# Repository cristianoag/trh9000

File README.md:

# TRH9000
The Yamaha V9990 based open-source video card for the MSX

## Introduction

If you ever spent just a few minutes on YouTube searching for MSX content, I bet you certainly found some footage covering the V9990. Well, not specifically the V9990 chip, but video cards based on it.

The first video card based on the unreleased, kind of obscure Yamaha V9990 VDP chip was the Graphics9000 (or GFX9000). The GFX9000 is (was) a graphics expansion device for MSX computers developed by Sunrise in 1994.

It was designed as an expansion cartridge for the MSX standard that can be installed in a slot on a computer that also connects to the computer’s video output and monitor. The device works as an additional independent video controller.

The device is based on the Yamaha V9990 video controller (VDP). The chip was designed specifically for use in computers of the alleged but not implemented (by the time of this writing) MSX3 standard. The V9990 is not backward compatible with the V99x8 chips, and thus cannot be used as the main video controller of standard MSX-compatible computers.

## The TRH9000

TRH9000 is an open-source implementation of the GFX9000, representing a community-driven effort to document everything necessary to build MSX cartridges that can run V9990 software.

| PCB Front | PCB Back |
| --- | --- |
|  |  |

The goal is to make those cards more accessible and improve the amount of software available for it. 

## Technical Information

The TRH9000 is a graphics expansion cartridge designed for MSX computers that was developed by a community of MSX enthusiasts as an open-source implementation of the GFX9000. 

### Selection Logic
For the TRH9000, the control logic is implemented by two ICs. According to the not exhaustive list of IO ports documented [here](https://www.msx.org/wiki/I/O_Ports_List). The IO ports used the by an GFX9000 compatible cartridge must be 60h~6Fh*. The 74LS138 IC on the board performs the selection of those IO ports and with the aid of the 74LS32 performs the activation of the appropriate signals on the V9990 chip.

> **Note:** Very important to use the 74LS138 and 74LS32 ICs. The 74HC138 and 74HC32 are not 100% compatible with the logic levels used by old MSX computers and if used, the cartridge may not work properly. 74HCT138 and 74HCT32 are also compatible with the old logic levels and can be used as a replacement.

### RAM chips

The KM428C256 RAM chip is the primary memory module used in the TRH9000. It is a CMOS 256K x 8 bit dual-port dynamic random-access memory (DRAM) chip that serves as the primary memory module in the cartridge. We use two memory chips, wired to the Yamaha V9990 VDP.

### Connectors

On its latest version, the TRH9000 features three types of video output connectors: a DB15 RGB/VGA connector, a RCA composite connector and a mini-DIN 4 SVideo connector. The DB15 connector is a standard video connector that supports VGA, and RGB, making it a versatile choice for connecting to various types of displays. The SVIDEO signal, on the other hand, is a video signal that carries the chrominance and luminance components of the video separately, resulting in a higher quality image than composite video that is output on the RCA connector. 

### Video Output

#### RGB 
The TRH9000 cartridge produces RGB signal with a horizontal frequency of 15.7KHz, which was the standard at the time of the V9990 chip's release. If you plan to connect the cartridge directly to your monitor using a VGA cable, it's important to ensure that your monitor supports synchronization at 15.7KHz.

You can see a list of modern monitors with support to 15.7KHz available at http://15khz.wikidot.com/

If you're not getting any image from the cartridge connector, it indicates that your monitor cannot sync at 15.7KHz. Typically, modern monitors can only sync at frequencies above 31KHz.

In such a scenario, you will require an adapter to upscale the frequency, making it compatible with your monitor. These adapters are commonly used for vintage video games and are readily available in various marketplaces. Here are a few options to consider:

||Description|Link|
|--|--|--|
||TZT HamGeek GBSC Converter GBS Control Retro Video Game Signal Converter Gaming Accessory  |[Ali Express](https://s.click.aliexpress.com/e/_DcZRM6T)
||OSSC HDMI-Compatible Converter Open Source Scan Adapter Kit with Game Cable for Retro Game Consoles  |[Ali Express](https://s.click.aliexpress.com/e/_DnNQGvv)
||Retrotink 2X Scart | https://www.retrotink.com/product-page/retrotink-2x-scart

If you decide to use the Retrotink you will need a VGA to SCART cable. That is easy to solder and you need to connect the signals in the following way:

|VGA||SCART|Signal|
|-|-|-|-|
|1|-->|15 |Red
|2|-->|11| Green
|3|--> |7 |Blue
|5|--> |21 |GND
|13|-->|20| Sync

By request of the community, a jumper was included on the latest PCB version to provide optionally 5V on the pin 9 of the VGA connector. This is useful for those who want to use build a SCART cable that depending on the monitor may require 5V in some pins. 

The jumper is located on the back of the PCB and is labeled as "JP1". The default position is open, so if you need to use it, you will need to close it with a solder blob.

Here is a diagram of the DH15 connector:

#### S-Video and Composite

The TRH9000 cartridge provides support for both S-Video and Composite video outputs. These video signals are transmitted through respective connectors that are located on the upper edge of the cartridge PCB. 

## Bill of Materials

[TRH9000 Interactive BOM](https://htmlpreview.github.io/?https://github.com/cristianoag/trh9000/blob/main/Hardware/Kicad/TRH9000_1.7/bom/ibom.html)

|References|Value|Footprint|Qtd|Link|
|-|-|-|-|-|
|C1, C6, C7, C8, C17, C19, C20, C22, C24	|0.1uF	|C_0805_2012Metric	|9|[Ali Express](https://s.click.aliexpress.com/e/_DkAAT2J)
|C9, C11, C12, C13, C14, C15, C26|	220uF	|CP_EIA-3528-15_AVX-H|	7|[Ali Express](https://s.click.aliexpress.com/e/_DCrPttV)
|C3, C4	|27pF|	C_0805_2012Metric|	2|[Ali Express](https://s.click.aliexpress.com/e/_DkAAT2J)
|C5, C10|	47pF	|C_0805_2012Metric|	2|[Ali Express](https://s.click.aliexpress.com/e/_DkAAT2J)
|C16, C18|	1uF	|C_0805_2012Metric	|2|[Ali Express](https://s.click.aliexpress.com/e/_DkAAT2J)
|C23, C25|	10nF|	C_0805_2012Metric|	2|[Ali Express](https://s.click.aliexpress.com/e/_DkAAT2J)
|C2|	10uF|	C_0805_2012Metric	|1|[Ali Express](https://s.click.aliexpress.com/e/_DkAAT2J)
|C21|	47uF|	CP_EIA-3528-15_AVX-H|	1|[Ali Express](https://s.click.aliexpress.com/e/_DCrPttV)
|R1, R3, R4, R5, R6, R10|	4K7	|R_0805_2012Metric|	6|[Ali Express](https://s.click.aliexpress.com/e/_DEyTmBN)
|R14, R15, R16, R17, R18, R19|	75R	|R_0805_2012Metric|	6|[Ali Express](https://s.click.aliexpress.com/e/_DEyTmBN)
|R20,R21,R22|470R|R_0805_2012Metric|3|[Ali Express](https://s.click.aliexpress.com/e/_DEyTmBN)
|R7, R12|	2K2	|R_0805_2012Metric|	2|[Ali Express](https://s.click.aliexpress.com/e/_DEyTmBN)
|			R2	|10M	|R_0805_2012Metric|	1|[Ali Express](https://s.click.aliexpress.com/e/_DEyTmBN)
|			R8	|1K	|R_0805_2012Metric|	1|[Ali Express](https://s.click.aliexpress.com/e/_DEyTmBN)
|			R9	|100R	|R_0805_2012Metric|	1|[Ali Express](https://s.click.aliexpress.com/e/_DEyTmBN)
|			R11	|220R	|R_0805_2012Metric	|1|[Ali Express](https://s.click.aliexpress.com/e/_DEyTmBN)
|			R13	|3K3|	R_0805_2012Metric	|1|[Ali Express](https://s.click.aliexpress.com/e/_DEyTmBN)
|			L1, L2|	4.7uH|	L_0805_2012Metric	|2|[Ali Express](https://s.click.aliexpress.com/e/_Dern3vN)
|			U4, U5	|KM428C256	|SOJ-40_400mil|	2|[UT Source](https://www.utsource.net/itm/p/781989.html)
|			U1	|74HC138	|SO-16_3.9x9.9mm_P1.27mm	|1|[Ali Express](https://s.click.aliexpress.com/e/_De0MrAf)
|			U2	|74HC32	|SO-14_3.9x8.65mm_P1.27mm|	1|[Ali Express](https://s.click.aliexpress.com/e/_DlCjJDN)
|			U3|	V9990|	LQFP-128_28x28mm_P0.8mm	|1|[The Retro Hacker Store](https://theretrohacker.com/product/v9990-non-vga-video-controller-ic-qfp-128/)
|			U6	|CXA2075M	|SOP-24_7.5x15.4mm_P1.27mm|	1|[Ali Express](https://s.click.aliexpress.com/e/_DBjZMTN)
|			Y1	|21.47727Mhz	|Crystal_HC49-U_Vertical|	1|[Ali Express](https://s.click.aliexpress.com/e/_DDj3q9t)
|			X1	|14.31818MHz|	Oscillator_DIP-4|	1|[Ali Express](https://s.click.aliexpress.com/e/_DEBzKw3)
|			RV1, RV2, RV3	|500R	|Potentiometer_Bourns_3314G_Vertical	|3|[Ali Express](https://s.click.aliexpress.com/e/_DnebEdD)
|			Q1	|BC817	|SOT-23	|1|[Ali Express](https://s.click.aliexpress.com/e/_DBlTES3)
|			J4	|S-Video	|Mini DIN 4 Pin Connector | 1 | [Ali Express](https://s.click.aliexpress.com/e/_De7X4Ud)
|			J2	|RGB	|DSUB-15-HD_Female_Horizontal	|1|[Ali Express](https://s.click.aliexpress.com/e/_DntckRl)
|            J3	|Composite	|RCA-2_Horizontal	|1|[Ali Express](https://s.click.aliexpress.com/e/_DBxnR6d)

## Community Contributions

There are a few folks activelly helping with the project and I would like to call them out here:

* Alexandre Souza
* Doomn00b
* Darlei Duarte
* lintweaker
* Luciano Sturaro
* MetalGear2
* sdsnatcher73
* sdsnatcher
* Thiago Valença
* Wagner Tavares

## License 

This work is licensed under a [Creative Commons Attribution-NonCommercial-ShareAlike 4.0 International License](http://creativecommons.org/licenses/by-nc-sa/4.0/).

* If you remix, transform, or build upon the material, you must distribute your contributions under the same license as the original.
* You may not use the material for commercial purposes.
* You must give appropriate credit, provide a link to the license, and indicate if changes were made. You may do so in any reasonable manner, but not in any way that suggests the licensor endorses you or your use.

**ATTENTION**

This project was made for the retro community and not for commercial purposes. So only retro hardware forums and individual people can build this project.

THE SALE OF ANY PART OF THIS PROJECT WITHOUT EXPRESS AUTHORIZATION IS PROHIBITED!

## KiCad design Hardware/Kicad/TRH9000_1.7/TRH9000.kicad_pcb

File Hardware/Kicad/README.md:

# TRH9000
The Yamaha V9990 based open-source video card for the MSX

## Kicad Project Files

* MSX_Breadboard_Large_V9990/ - This project involves a prototype cartridge designed to validate the main TRH9000 circuit. The board project is based on the work done by Alexey Wierzbowsky and has been adapted to include pads for memory chips, V9990, and two different video chips. We are currently testing the Sony RGB encoder (CXA2075M) and the TI Auto-Detecting SD/HD/PC Video Sync Separator (LMH1980) to generate the video signal.

* TRH9000.cxa2075/ - This is the main TRH9000 circuit and PCB project that utilizes the Sony CXA2075 RGB encoder. This board has been tested and is fully functional, delivering very good image quality.

* TRH9000.lmh1980/ - This is another version of the main TRH9000 circuit and PCB project that uses the Texas LMH1980 sync separator. While this board is functional, it doesn't follow the best practices when connecting to the RGB.

* TRH9000S/ - The TRH9000S is the latest version of the main TRH9000 circuit and PCB board project. This version features two connectors, including one DIN8 270 to receive input from the MSX computer and another DB15 as the RGB/VGA output. However, please note that this board also uses the LMH1980 and does not follow the best practices when connecting to the RGB. As a result, I recommend that you not use this board on your vintage hardware, as it is still under development and may cause harm to your computers.
* 
## License 

This work is licensed under the CERN OHL-S v2. You may redistribute and modify this project and its documentation under the terms of the CERN-OHL-S v2.

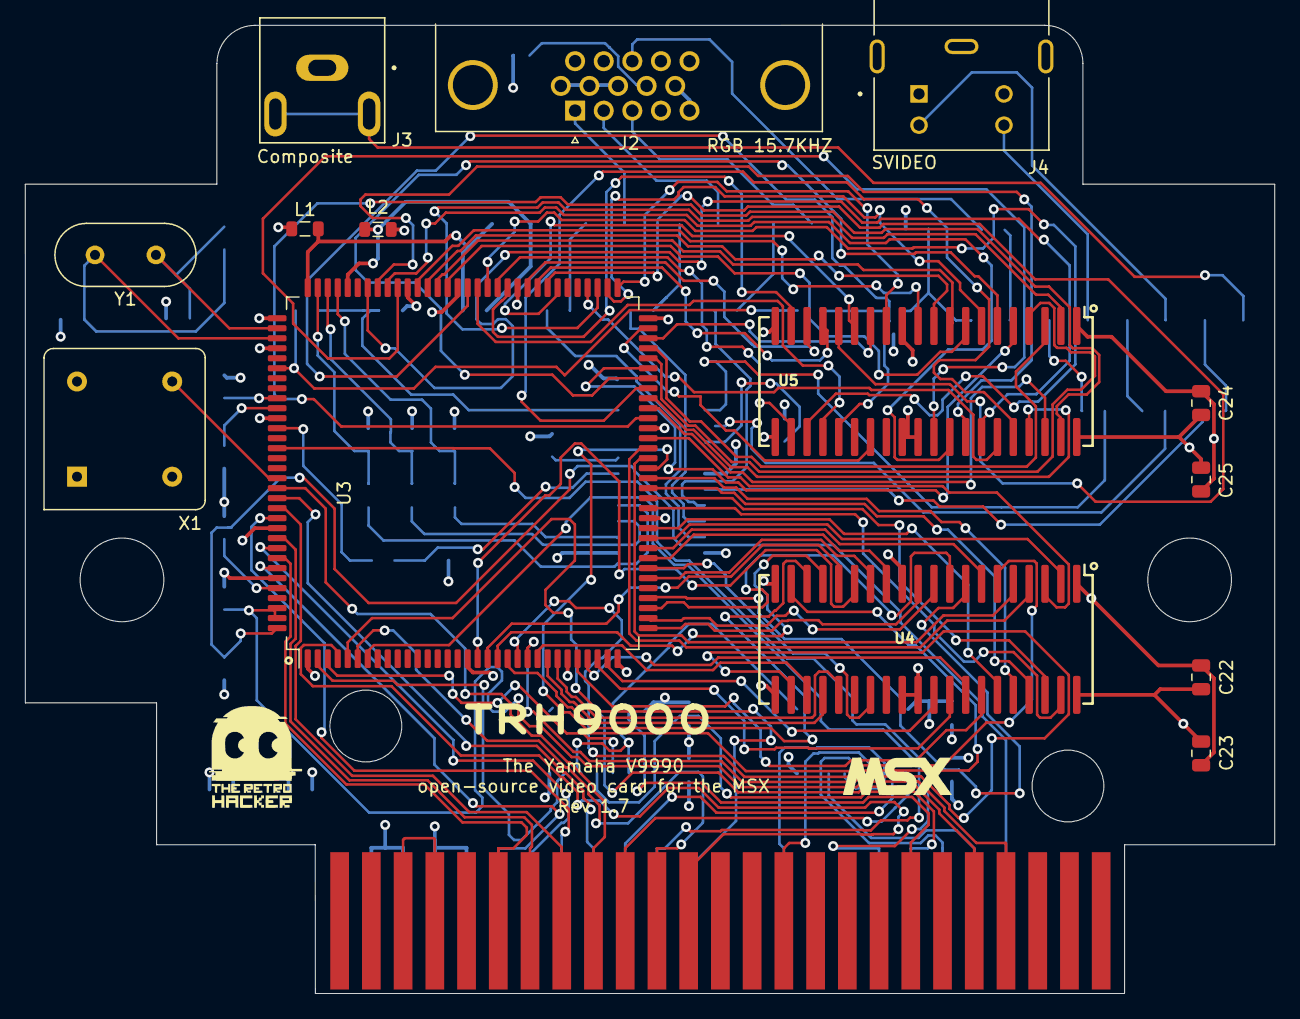
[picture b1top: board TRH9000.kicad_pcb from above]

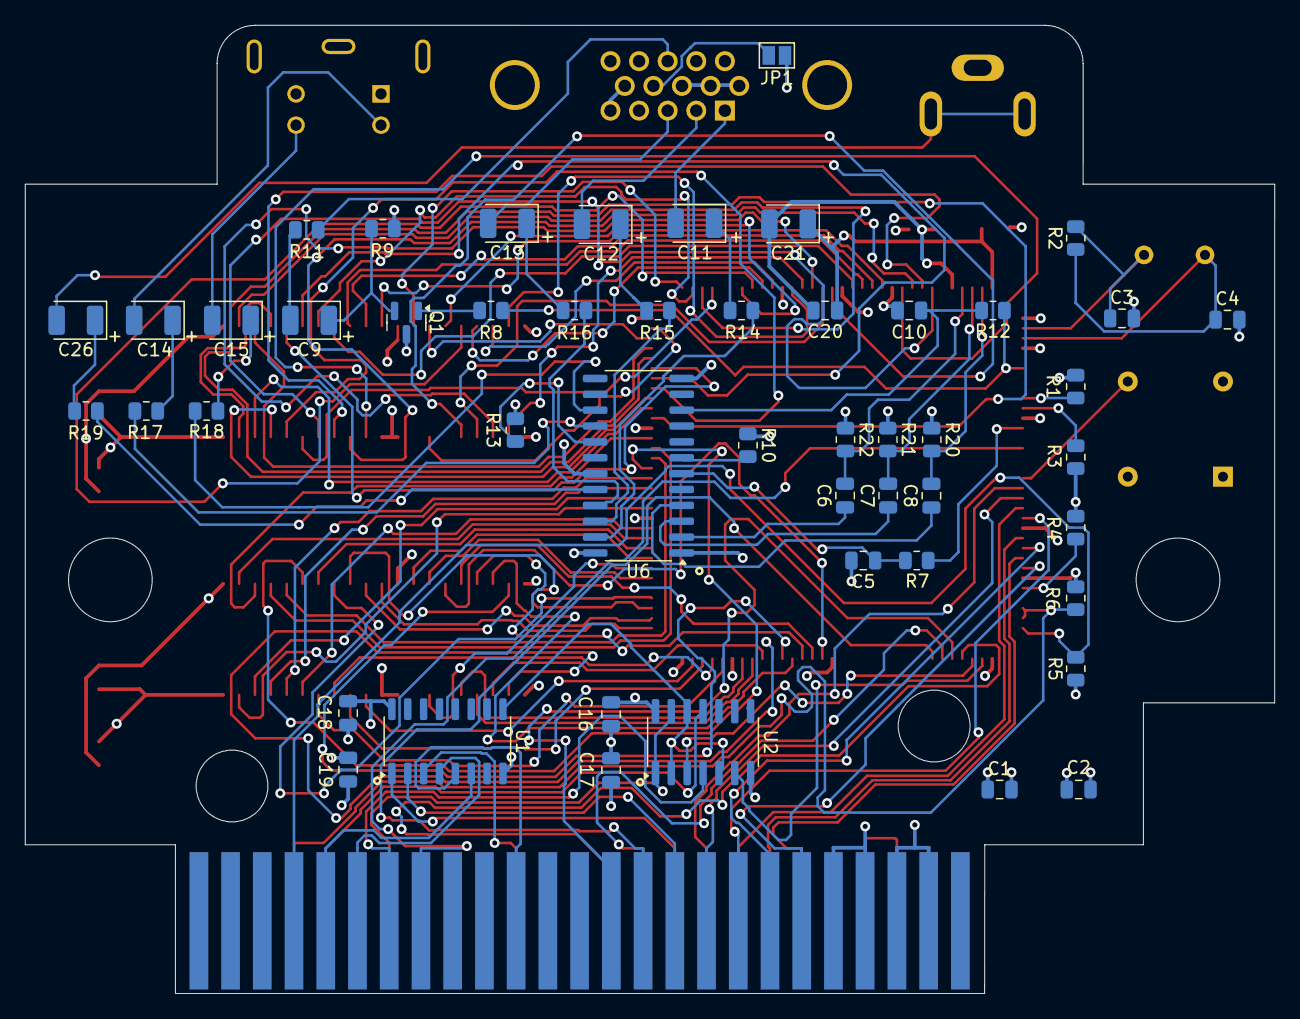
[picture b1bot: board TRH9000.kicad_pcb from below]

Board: 4 copper layers, 100.0 x 77.5 mm, 65 parts (49 on the bottom side), 135 nets.

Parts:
BUS1: MSX_SLOT_EDGE-CON; msx_cartridge
C1, C17, C19, C22, C24: 0.1uF; C_0805_2012Metric
C2: 10uF; C_0805_2012Metric
C3, C4: 27pF; C_0805_2012Metric
C5, C10: 47pF; C_0805_2012Metric
C6, C7, C8, C20: 100nF; C_0805_2012Metric
C9, C11, C12, C13, C14, C15, C26: 220uF; CP_EIA-3528-15_AVX-H
C16, C18: 1uF; C_0805_2012Metric
C21: 47uF; CP_EIA-3528-15_AVX-H
C23, C25: 10nF; C_0805_2012Metric
J2: RGB; DSUB-15-HD_Female_Horizontal_P2.29x1.98mm_EdgePinOffset3.03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
J3: Composite; SWITCHCRAFT_PJRAN1X1U02AUX
J4: SVIDEO; CUI_MD-40SM
JP1: Jumper_2_Open; SolderJumper-2_P1.3mm_Open_Pad1.0x1.5mm
L1, L2: 4.7uH; L_0805_2012Metric
MSX1: LOGO
Q1: BC817; SOT-23
R1, R3, R4, R5, R6, R10: 4K7; R_0805_2012Metric
R2: 10M; R_0805_2012Metric
R7, R12: 2K2; R_0805_2012Metric
R8: 1K; R_0805_2012Metric
R9: 100R; R_0805_2012Metric
R11: 220R; R_0805_2012Metric
R13: 3K32 1%; R_0805_2012Metric
R14, R15, R16, R17, R18, R19: 75R; R_0805_2012Metric
R20, R21, R22: 470R; R_0805_2012Metric
U1: 74HC138; SO-16_3.9x9.9mm_P1.27mm
U2: 74HC32; SO-14_3.9x8.65mm_P1.27mm
U3: V9990; LQFP-128_28x28mm_P0.8mm
U4, U5: KM428C256; SOJ-40_400mil
U6: CXA2075M; SO-24_5.3x15mm_P1.27mm
X1: 14.31818MHz; Oscillator_DIP-8
Y1: 21.47727Mhz; Crystal_HC49-U_Vertical

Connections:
+5V: BUS1.45 (+5V), BUS1.47 (+5V), C1.1, C2.1, C16.1, C17.1, C18.1, C19.1, C22.1, C23.2, C24.1, C25.2, JP1.1 (A), L1.1, Q1.3 (C), R1.1, R3.2, R4.1, R5.1, R6.1, R10.1, R13.1, U1.16 (VCC), U2.14 (VCC), U3.27 (VDD), U3.53 (VDD), U3.81 (VDD), U3.97 (VDD), U3.123 (VDD), U4.1 (VCC), U4.20 (VCC), U5.1 (VCC), U5.20 (VCC), U6.12 (VCC), U6.19 (VCC), X1.1 (EN), X1.8 (Vcc)
+5VA: C20.1, C21.1, L1.2, U3.96 (VDDA)
/A0: BUS1.28 (A0), U3.4 (MODE0)
/A1: BUS1.27 (A1), U3.5 (MODE1)
/A2: BUS1.30 (A2), U3.6 (MODE2)
/A3: BUS1.29 (A3), U3.7 (MODE3)
/A4: BUS1.32 (A4), U1.1 (A0)
/A5: BUS1.31 (A5), U1.2 (A1)
/A6: BUS1.22 (A6), U1.3 (A2)
/A7: BUS1.21 (A7), U1.5 (~G2B)
/D0: BUS1.34 (D0), U3.114 (CD0)
/D1: BUS1.33 (D1), U3.115 (CD1)
/D2: BUS1.36 (D2~), U3.116 (CD2)
/D3: BUS1.35 (D3), U3.117 (CD3)
/D4: BUS1.38 (D4), U3.119 (CD4)
/D5: BUS1.37 (D5), U3.120 (CD5)
/D6: BUS1.40 (D6), U3.121 (CD6)
/D7: BUS1.39 (D7), U3.122 (CD7)
/VDP/B: C8.2, R20.2, U3.95 (B/D1/CB1)
/VDP/G: C7.2, R21.2, U3.94 (G/D2/CB2)
/VDP/HRESET: R1.2, U3.105 (~HRESET/CB4)
/VDP/MCKIN: U3.113 (MCKIN), X1.5 (OUT)
/VDP/NTSC_CLK: R7.2, U3.108 (CB6/FSC)
/VDP/R: C6.2, R22.2, U3.93 (R/D3/CB3)
/VDP/V0A0: U3.26 (V0_A0/KA0), U4.25 (A0)
/VDP/V0A1: U3.25 (V0_A1/KA1), U4.24 (A1)
/VDP/V0A2: U3.24 (V0_A2/KA2), U4.23 (A2)
/VDP/V0A3: U3.23 (V0_A3/KA3), U4.22 (A3)
/VDP/V0A4: U3.22 (V0_A4/KA4), U4.19 (A4)
/VDP/V0A5: U3.21 (V0_A5/KA5), U4.18 (A5)
/VDP/V0A6: U3.20 (V0_A6/KA6), U4.17 (A6)
/VDP/V0A7: U3.19 (V0_A7/KA7), U4.16 (A7)
/VDP/V0A8: U3.18 (V0_A8/KA8), U4.15 (A8)
/VDP/V0D0: U3.36 (V0_D0/KD0), U4.8 (W0/DQ0)
/VDP/V0D1: U3.35 (V0_D1/KD1), U4.9 (W1/DQ1)
/VDP/V0D2: U3.34 (V0_D2/KD2), U4.10 (W2/DQ2)
/VDP/V0D3: U3.33 (V0_D3/KD3), U4.11 (W3/DQ3)
/VDP/V0D4: U3.31 (V0_D4/KD4), U4.31 (W4/DQ4)
/VDP/V0D5: U3.30 (V0_D5/KD5), U4.32 (W5/DQ5)
/VDP/V0D6: U3.29 (V0_D6/KD6), U4.33 (W6/DQ6)
/VDP/V0D7: U3.28 (V0_D7/KD7), U4.34 (W7/DQ7)
/VDP/V0S0: U3.52 (V0_S0), U4.3 (SDQ0)
/VDP/V0S1: U3.51 (V0_S1), U4.4 (SDQ1)
/VDP/V0S2: U3.50 (V0_S2), U4.5 (SDQ2)
/VDP/V0S3: U3.49 (V0_S3), U4.6 (SDQ3)
/VDP/V0S4: U3.48 (V0_S4), U4.36 (SDQ4)
/VDP/V0S5: U3.47 (V0_S5), U4.37 (SDQ5)
/VDP/V0S6: U3.46 (V0_S6), U4.38 (SDQ6)
/VDP/V0S7: U3.45 (V0_S7), U4.39 (SDQ7)
/VDP/V1A0: U3.80 (V1_A0), U5.25 (A0)
/VDP/V1A1: U3.79 (V1_A1), U5.24 (A1)
/VDP/V1A2: U3.78 (V1_A2), U5.23 (A2)
/VDP/V1A3: U3.77 (V1_A3), U5.22 (A3)
/VDP/V1A4: U3.76 (V1_A4), U5.19 (A4)
/VDP/V1A5: U3.74 (V1_A5), U5.18 (A5)
/VDP/V1A6: U3.73 (V1_A6), U5.17 (A6)
/VDP/V1A7: U3.72 (V1_A7), U5.16 (A7)
/VDP/V1A8: U3.71 (V1_A8), U5.15 (A8)
/VDP/V1D0: U3.82 (V1_D0), U5.8 (W0/DQ0)
/VDP/V1D1: U3.83 (V1_D1), U5.9 (W1/DQ1)
/VDP/V1D2: U3.84 (V1_D2), U5.10 (W2/DQ2)
/VDP/V1D3: U3.85 (V1_D3), U5.11 (W3/DQ3)
/VDP/V1D4: U3.87 (V1_D4), U5.31 (W4/DQ4)
/VDP/V1D5: U3.88 (V1_D5), U5.32 (W5/DQ5)
/VDP/V1D6: U3.89 (V1_D6), U5.33 (W6/DQ6)
/VDP/V1D7: U3.90 (V1_D7), U5.34 (W7/DQ7)
/VDP/V1S0: U3.61 (V1_S0), U5.3 (SDQ0)
/VDP/V1S1: U3.60 (V1_S1), U5.4 (SDQ1)
/VDP/V1S2: U3.59 (V1_S2), U5.5 (SDQ2)
/VDP/V1S3: U3.58 (V1_S3), U5.6 (SDQ3)
/VDP/V1S4: U3.57 (V1_S4), U5.36 (SDQ4)
/VDP/V1S5: U3.56 (V1_S5), U5.37 (SDQ5)
/VDP/V1S6: U3.55 (V1_S6), U5.38 (SDQ6)
/VDP/V1S7: U3.54 (V1_S7), U5.39 (SDQ7)
/VDP/VMREQ: R4.2, U3.124 (~VMREQ)
/VDP/VRESET: R3.1, U3.106 (~VRESET/CB5)
/VDP/X1: C3.1, R2.2, U3.98 (XTAL1), Y1.1
/VDP/X2: C4.1, R2.1, U3.99 (XTAL2), Y1.2
/VDP/~CSYNC: R8.2, R12.1, U3.102 (~CSYNC/FLM)
/VDP/~V0_CAS: U3.39 (~V0_CAS), U4.27 (~CAS)
/VDP/~V0_RAS: U3.38 (~V0_RAS), U4.14 (~RAS)
/VDP/~V0_SC: U3.42 (~V0_SC), U4.2 (SC)
/VDP/~V0_TR: U3.41 (~V0_TR/OE), U4.7 (~DT/~OE)
/VDP/~V0_WE: U3.40 (~V0_WE), U4.13 (~WB/~WE)
/VDP/~V1_CAS: U3.63 (~V1_CAS), U5.27 (~CAS)
/VDP/~V1_RAS: U3.62 (~V1_RAS), U5.14 (~RAS)
/VDP/~V1_SC: U3.67 (V1_SC), U5.2 (SC)
/VDP/~V1_SOE: U3.68 (~V1_SOE), U5.35 (~SE)
/VDP/~V1_TR: U3.66 (~V1_TR/OE), U5.7 (~DT/~OE)
/VDP/~V1_WE: U3.65 (~V1_WE), U5.13 (~WB/~WE)
/VDP/~VDPR: U2.3 (1Y), U3.3 (~CSR)
/VDP/~VDPW: U2.6 (2Y), U3.2 (~CSW)
/VDP/~VO_SOE: U3.43 (~V0_SOE), U4.35 (~SE)
/VIDEO/BOUT: C13.2, J2.3
/VIDEO/COUT: C15.2, J4.4
/VIDEO/CSYNCO: J2.13, R11.1
/VIDEO/CVOUT: C26.2, J3.2, J3.3
/VIDEO/GOUT: C12.2, J2.2
/VIDEO/ROUT: C11.2, J2.1
/VIDEO/YOUT: C14.2, J4.3
/~BUSDIR: BUS1.10 (~BUSDIR), U2.11 (4Y)
/~INT: BUS1.8 (~INT), R6.2, U3.126 (~INT0), U3.127 (~INT1)
/~IORQ: BUS1.11 (~IORQ), U1.4 (~G2A)
/~M1: BUS1.9 (~M1), U1.6 (G1)
/~RD: BUS1.14 (~RD), U2.1 (1A), U2.13 (4B)
/~RESET: BUS1.15 (~RESET), U3.110 (~RESET)
/~WAIT: BUS1.7 (~WAIT), R5.2, U3.128 (~WAIT)
/~WR: BUS1.13 (~WR), U2.4 (2A)
GND: BUS1.41 (GND), BUS1.43 (GND), C1.2, C2.2, C3.2, C4.2, C5.2, C10.2, C16.2, C17.2, C18.2, C19.2, C22.2, C23.1, C24.2, C25.1, J2.5, J2.6, J2.7, J2.8, J2.10, J3.1, J4.1, J4.2, J4.S1 (SHIELD), J4.S2 (SHIELD), J4.S3 (SHIELD), L2.1, R9.2, R20.1, R21.1, R22.1, U1.8 (GND), U2.7 (GND), U3.1 (VSS), U3.17 (VSS), U3.32 (VSS), U3.44 (VSS), U3.64 (VSS), U3.75 (VSS), U3.86 (VSS), U3.100 (VSS), U3.107 (VSS), U3.118 (VSS), U4.12 (VSS), U4.21 (VSS), U4.29 (DSF), U4.30 (VSS), U4.40 (VSS), U5.12 (VSS), U5.21 (VSS), U5.29 (DSF), U5.30 (VSS), U5.40 (VSS), U6.1 (GND), U6.24 (GND), X1.4 (GND)
GNDA: C20.2, C21.2, L2.2, U3.92 (VSSA)
unnamed: BUS1.44 (SW1), BUS1.46 (SW2)
unnamed: C9.2, R11.2
unnamed: C11.1, R14.1
unnamed: C12.1, R15.1
unnamed: C13.1, R16.1
unnamed: C14.1, R17.1
unnamed: C15.1, R18.1
unnamed: C26.1, R19.1
unnamed: J2.9, JP1.2 (B)
unnamed: Q1.1 (B), R8.1
unnamed: C9.1, Q1.2 (E), R9.1
unnamed: U1.9 (~Y6), U2.2 (1B), U2.5 (2B), U2.12 (4A)
unnamed: C8.1, U6.4 (BIN)
unnamed: R16.2, U6.21 (BOUT)
unnamed: R18.2, U6.15 (COUT)
unnamed: R19.2, U6.20 (CVOUT)
unnamed: C7.1, U6.3 (GIN)
unnamed: R15.2, U6.22 (GOUT)
unnamed: R10.2, U6.7 (NPIN)
unnamed: C6.1, U6.2 (RIN)
unnamed: R14.2, U6.23 (ROUT)
unnamed: C5.1, R7.1, U6.6 (SCIN)
unnamed: C10.1, R12.2, U6.10 (SYNCIN)
unnamed: R17.2, U6.16 (YOUT)
unnamed: R13.2, U6.17 (YTRAP)

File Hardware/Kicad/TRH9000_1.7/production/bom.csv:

Designator,Footprint,Quantity,Value,LCSC Part #
"C1, C17, C19, C22, C24",0805,5,0.1uF,
"C10, C5",0805,2,47pF,
"C11, C12, C13, C14, C15, C26, C9",CP_EIA-3528-15_AVX-H,7,220uF,
"C16, C18",0805,2,1uF,
C2,0805,1,10uF,
"C20, C6, C7, C8",0805,4,100nF,
C21,CP_EIA-3528-15_AVX-H,1,47uF,
"C23, C25",0805,2,10nF,
"C3, C4",0805,2,27pF,
J2,DSUB-15-HD_Female_Horizontal_P2.29x1.98mm_EdgePinOffset3.03mm_Housed_MountingHolesOffset4.94mm,1,RGB,
J3,SWITCHCRAFT_PJRAN1X1U02AUX,1,Composite,
J4,CUI_MD-40SM,1,SVIDEO,
JP1,SolderJumper-2_P1.3mm_Open_Pad1.0x1.5mm,1,Jumper_2_Open,
"L1, L2",0805,2,4.7uH,
Q1,SOT-23,1,BC817,
"R1, R10, R3, R4, R5, R6",0805,6,4K7,
R11,0805,1,220R,
"R12, R7",0805,2,2K2,
R13,0805,1,3K32 1%,
"R14, R15, R16, R17, R18, R19",0805,6,75R,
R2,0805,1,10M,
"R20, R21, R22",0805,3,470R,
R8,0805,1,1K,
R9,0805,1,100R,
U1,SO-16_3.9x9.9mm_P1.27mm,1,74HC138,74HC138
U2,SO-14_3.9x8.65mm_P1.27mm,1,74HC32,74HC32
U3,LQFP-128_28x28mm_P0.8mm,1,V9990,V9990
"U4, U5",SOJ-40_400mil,2,KM428C256,
U6,SO-24_5.3x15mm_P1.27mm,1,CXA2075M,
X1,Oscillator_DIP-8,1,14.31818MHz ,CE3291-14.318180
Y1,Crystal_HC49-U_Vertical,1,21.47727Mhz,

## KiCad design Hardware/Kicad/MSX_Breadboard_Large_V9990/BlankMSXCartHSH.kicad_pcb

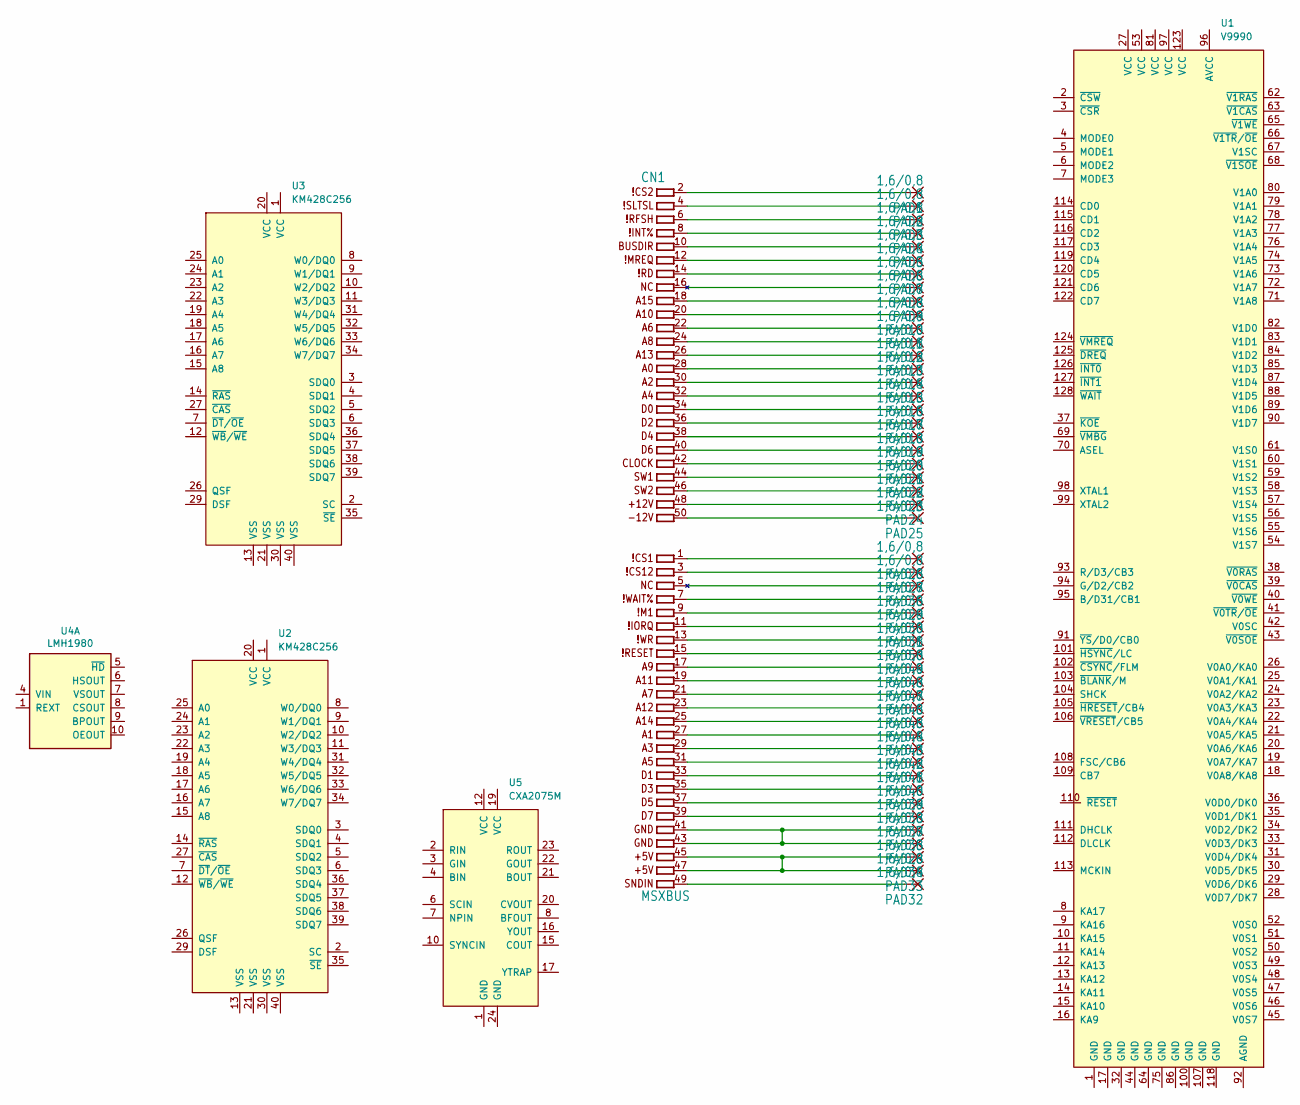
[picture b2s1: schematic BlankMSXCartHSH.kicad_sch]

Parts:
CN1: MSXBUS; MSXBUS_EDGECONN
PAD1, PAD2, PAD3, PAD4, PAD5, PAD6, PAD7, PAD8, PAD9, PAD10, PAD11, PAD12, PAD13, PAD14, PAD15, PAD16, PAD17, PAD18, PAD19, PAD20, PAD21, PAD22, PAD23, PAD24, PAD25, PAD26, PAD27, PAD28, PAD29, PAD30, PAD31, PAD32, PAD33, PAD34, PAD35, PAD36, PAD37, PAD38, PAD39, PAD40, PAD41, PAD42, PAD43, PAD44, PAD45, PAD46, PAD47, PAD48, PAD49, PAD50: 1,6/0,8; 1,6_0,8
U1: V9990; QFP-128_28x28_Pitch0.8mm
U2, U3: KM428C256; SOJ-40_400mil
U4: LMH1980; VSSOP-10_3x3mm_P0.5mm; MPN LMH1980MM/NOPBCT
U5: CXA2075M; SOP-24_7.5x15.4mm_P1.27mm

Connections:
+5V: CN1.45 (45.+5V), CN1.47 (47.+5V), PAD33.1, PAD34.1
GND: CN1.41 (41.GND), CN1.43 (43.GND), PAD28.1, PAD35.1
unnamed: CN1.2 (2.~CS2), PAD1.1
unnamed: CN1.4 (4.~SLTSL), PAD2.1
unnamed: CN1.6 (6.~RFSH), PAD3.1
unnamed: CN1.8 (8.~INT%), PAD4.1
unnamed: CN1.10 (10.BUSDIR), PAD5.1
unnamed: CN1.12 (12.~MREQ), PAD6.1
unnamed: CN1.14 (14.~RD), PAD7.1
unnamed: CN1.16 (16.NC), PAD8.1
unnamed: CN1.18 (18.A15), PAD9.1
unnamed: CN1.20 (20.A10), PAD10.1
unnamed: CN1.22 (22.A6), PAD11.1
unnamed: CN1.24 (24.A8), PAD12.1
unnamed: CN1.26 (26.A13), PAD13.1
unnamed: CN1.28 (28.A0), PAD14.1
unnamed: CN1.30 (30.A2), PAD15.1
unnamed: CN1.32 (32.A4), PAD16.1
unnamed: CN1.34 (34.D0), PAD17.1
unnamed: CN1.36 (36.D2), PAD18.1
unnamed: CN1.38 (38.D4), PAD19.1
unnamed: CN1.40 (40.D6), PAD20.1
unnamed: CN1.42 (42.CLOCK), PAD21.1
unnamed: CN1.44 (44.SW1), PAD22.1
unnamed: CN1.46 (46.SW2), PAD23.1
unnamed: CN1.48 (48.+12V), PAD24.1
unnamed: CN1.50 (50.-12V), PAD25.1
unnamed: CN1.1 (1.~CS1), PAD26.1
unnamed: CN1.3 (3.~CS12), PAD27.1
unnamed: CN1.5 (5.NC), PAD36.1
unnamed: CN1.7 (7.~WAIT%), PAD29.1
unnamed: CN1.9 (9.~M1), PAD30.1
unnamed: CN1.11 (11.~IORQ), PAD31.1
unnamed: CN1.49 (49.SNDIN), PAD32.1
unnamed: CN1.39 (39.D7), PAD37.1
unnamed: CN1.37 (37.D5), PAD38.1
unnamed: CN1.35 (35.D3), PAD39.1
unnamed: CN1.33 (33.D1), PAD40.1
unnamed: CN1.31 (31.A5), PAD41.1
unnamed: CN1.29 (29.A3), PAD42.1
unnamed: CN1.27 (27.A1), PAD43.1
unnamed: CN1.25 (25.A14), PAD44.1
unnamed: CN1.23 (23.A12), PAD45.1
unnamed: CN1.21 (21.A7), PAD46.1
unnamed: CN1.19 (19.A11), PAD47.1
unnamed: CN1.17 (17.A9), PAD48.1
unnamed: CN1.15 (15.~RESET), PAD49.1
unnamed: CN1.13 (13.~WR), PAD50.1

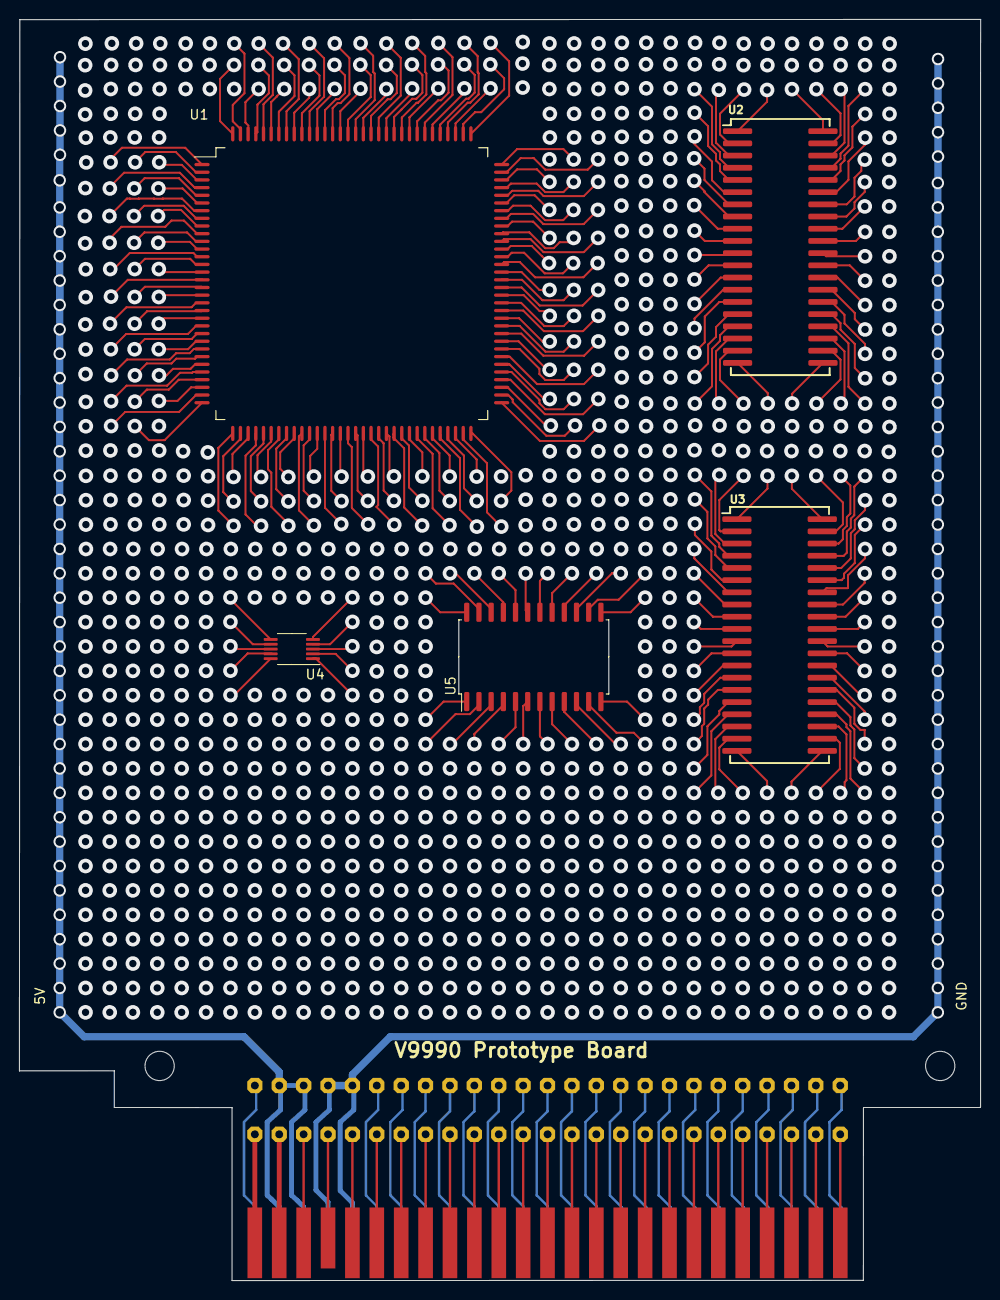
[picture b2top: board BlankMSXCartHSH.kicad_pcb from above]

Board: 2 copper layers, 100.1 x 131.3 mm, 58 parts (0 on the bottom side), 48 nets.

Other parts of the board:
@HOLE0, @HOLE1: (no value)

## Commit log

2022-08-02 Create LICENSE
2022-08-03 Revision 0 upload
2022-08-03 Readme.md update
2022-08-03 Uploading docs
2022-08-03 .gitignore
2022-08-03 rermoving backups
2022-08-03 Footprint for the V9990
2022-08-03 Trimpots for the RGB coming from V9990
2022-08-04 REV0 - Footprint review
2022-08-04 Updates on README
2022-08-04 Footprint adjusts
2022-08-09 Initial component placement on the PCB.
2022-08-11 Routing 1. First 3d view of the current PCB.
2022-08-11 Changed Git-ignore to standard Kicad-format, added a changelog, started adding navigation-bookmarks to the datasheets.
2022-08-15 Many changes, among them, replacing the Composite out with SCART-rgb.
2022-08-21 Multiple updates. Routing. Almost finished routing for the VDP. Moved back the footprint for the 14mhz oscillator to THT as it is easier to find outside US/Europe and I have a bunch laying around her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
2022-08-21 PCB image
2022-08-21 Routing, readme, etc
2022-08-21 images
2022-08-21 README edits
2022-08-21 README
2022-08-21 MSX logo
2022-08-22 Small correction on the front silkscreen
2022-09-10 Prototype board. Fixes to the main project. Readme updates.
2022-09-21 Updates during tests with prototype
2022-10-04 Multiple changes. Check the dev log.
2022-10-04 Small fix to the prototype MSX_Breadboard_Large_V9990 board
2022-11-01 Multiple changes.
2022-11-01 Minor adjustments
2022-11-27 Changes on README.md
2022-11-27 Board Images
2022-11-27 TRH9000S
2022-11-27 Datasheets
2022-12-25 Moving caps to avoid conflict with sockets, uploading image with issue when superimposing
2022-12-26 board review to use the CXA2075 instead of the LMH1980
2022-12-26 changes on the readmes
2022-12-26 documentation
2023-02-28 small fix on the YTRAP to use internal for NTSC.
2023-03-01 Updating readme files
2023-03-01 new gerber files and BOM
2023-03-01 Uploading labels
2023-03-01 fix README
2023-03-24 board fabrication
2023-03-26 final cartridge image
2023-04-19 small fix on the B silkscreen
2023-07-11 new gerber.zip
2023-07-16 Small fix on the silk
2023-09-24 Info on the Video Signal, links for the BOM, Availability of the V9990 on the store.
2023-10-22 Fix on VRAM wiring
2023-10-22 Jumper to provide 5V to SCART cables
2023-10-22 Fabrication artifacts v1.3
2023-10-22 Note on the readme file about the 5V jumper.
2023-10-22 Readme update
2023-10-22 Interactive bom
2023-11-05 Exposing composite, footprint and silk corrections
2023-11-05 Instructions to build S-Video and Composite cables
2023-11-05 Images for the readme file
2023-11-05 BOM adjustments
2023-11-05 Images for the README, mention to the XHB connector.
2023-11-13 Including the RGB pinout
2023-11-13 S-Video cable instructions
2023-11-13 RGB_PINOUT
2023-11-13 RGB PINOUT
2023-12-31 SW1-SW2 jumper. v1.41
2024-02-22 Updates to have Svideo and Composite exposed via appropriate connectors
2024-02-22 lock removal
2024-03-03 REAME and license update
2024-03-19 Fix on pins 12 and 13 of the VRAM
2024-06-04 kicad 8 migration. minor positioning for the connectors
2024-06-15 Fix for B&W when turbo is enabled is specific computers.
2024-06-15 v1.7 BOM on Readme
2025-01-01 Content organization. README.MD update.

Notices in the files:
Hardware/Kicad/TRH9000_1.7/TRH9000.kicad_pcb:
Shared under CERN-OHL-S license
